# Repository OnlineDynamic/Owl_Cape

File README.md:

# Owl_Cape
Raspberry Pi (SMI Driven) FPP WS2811 based ch16 Pixel Controller Cape

Building on the great work of the Falcon FPP project, numerous open hardware pixel controllers and the clever brain behind this blog: https://iosoft.blog/2020/09/29/raspberry-pi-multi-channel-ws2812/

This project is looking to create a simple low cost 16ch Raspberry PI Cape to run on FPP using SMI interface of a 'Raspberry Pi Zero 2 W' (and potentially then expand out to supporting other Pi's with the 40PIN Header).  The aspiration is for the final code for the cape to be included in the FPP project and the xLights project to make a low cost easy to use pixel controller for LED pixel light shows which will benefit as the FPP project evolves its functionality.

## Basic Spec of Cape

- 12V DC in only (fused at xx Amps)
- PI Mounts on PCB
- 40 Pin Header for attaching to RPI via a ribbon cable (allow easy removal of PI)
- Power the RPI via Header pins
- 16 Ch of LED (WS2811) outputs individually fused at 5A running at 12V DC with SMD LED power indicators
- EEPROM onboard to identify CAPE to PI

## Potential Future expansion
- On board RJ45 Jack to connect wired ethernet to PI using USB test pads on PI
- Jumper to make LED voltage either 12V or 5V DC
- Basic LED Screen showing status

## Out of scope
- Any differential outputs

## Special Thanks to:
https://github.com/Kosh42/PCB-Designs/tree/main/Mirage for the inspiration

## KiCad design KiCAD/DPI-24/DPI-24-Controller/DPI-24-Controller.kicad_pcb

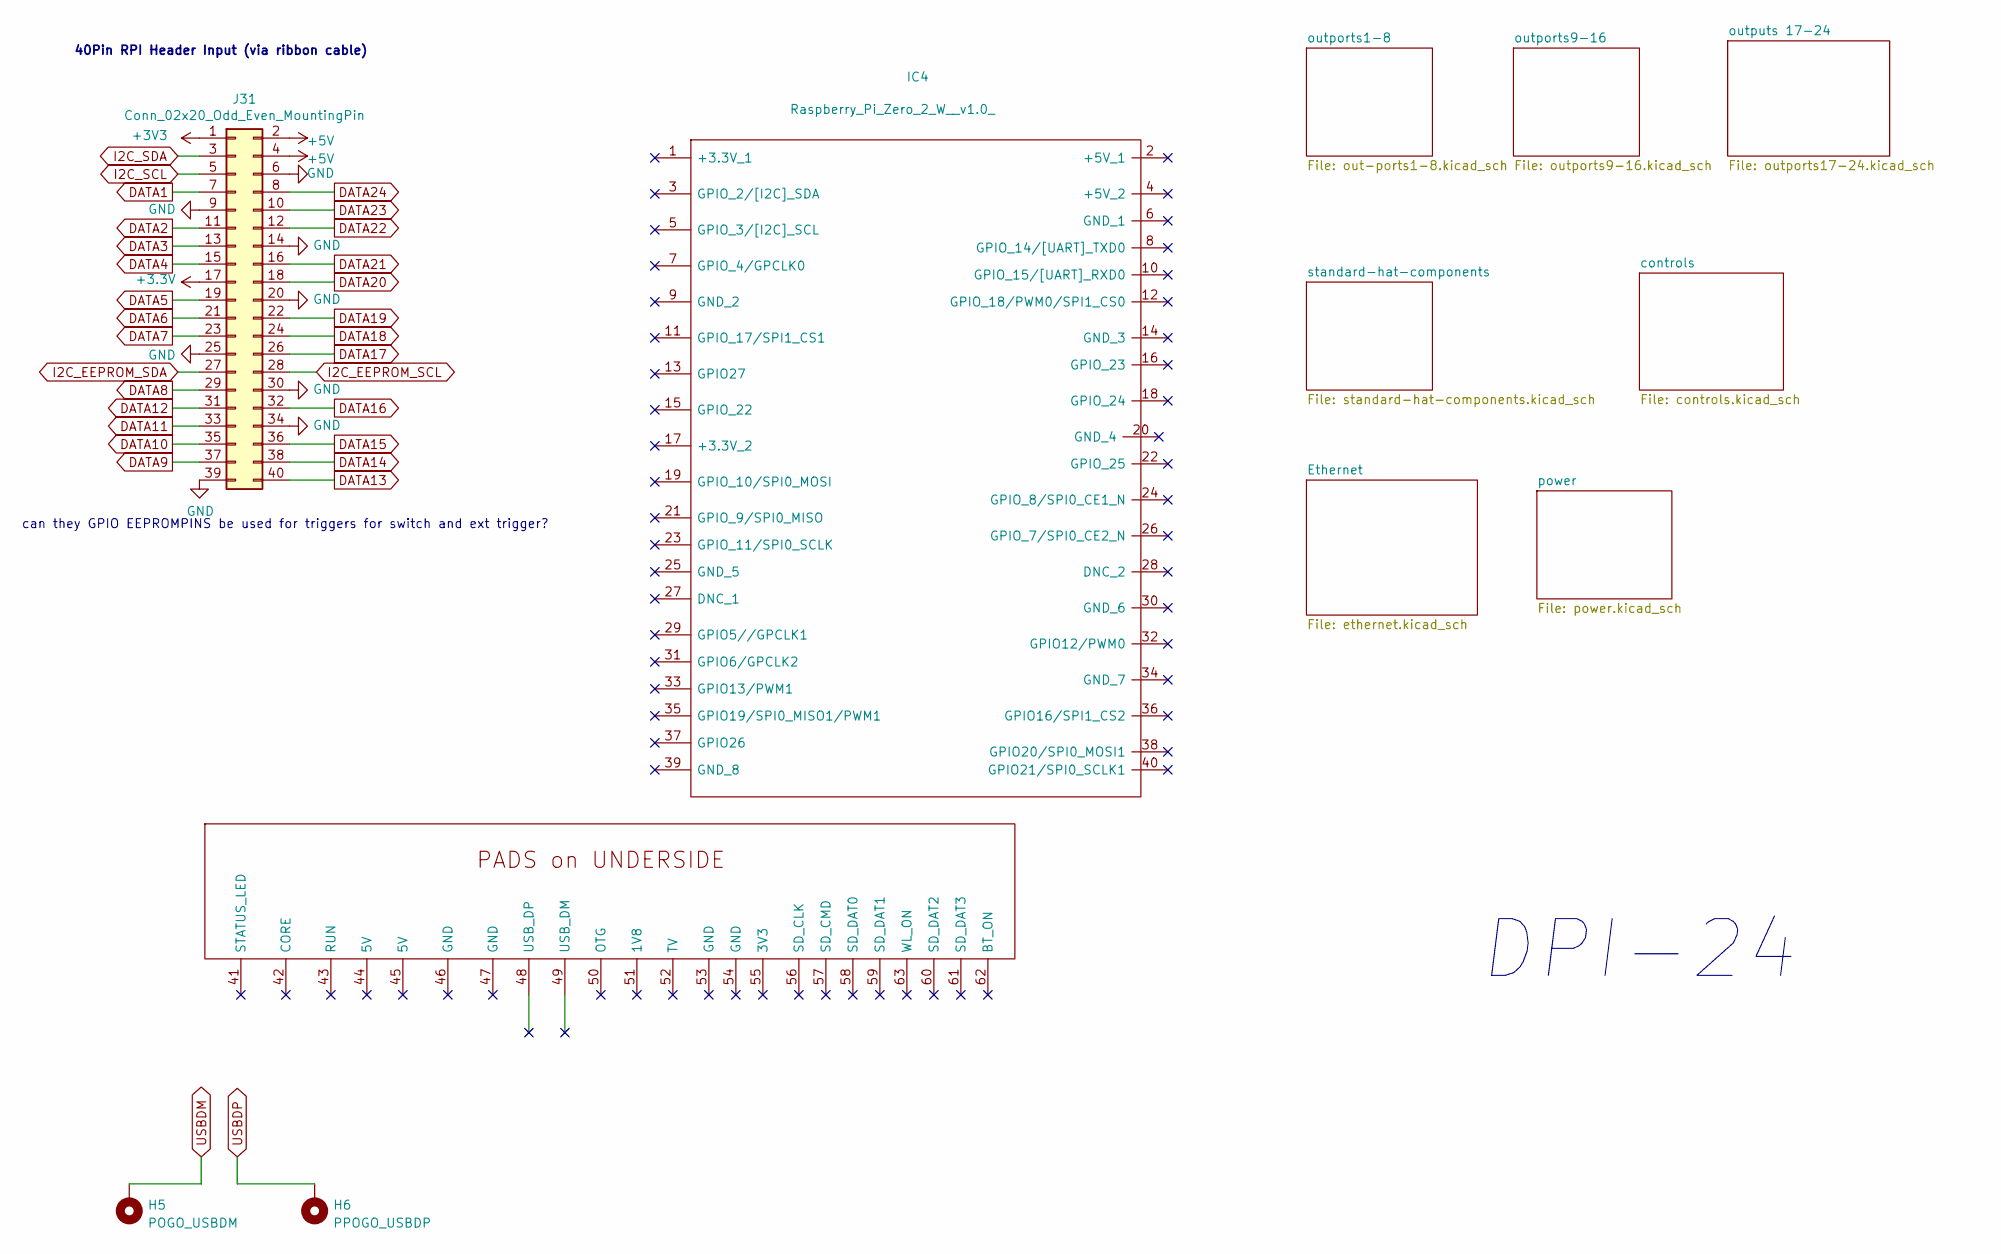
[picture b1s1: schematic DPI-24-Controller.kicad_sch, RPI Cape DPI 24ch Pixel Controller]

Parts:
H5: POGO_USBDM; POGO_D3.50mm_Drill0.9mm
H6: PPOGO_USBDP; POGO_D3.50mm_Drill0.9mm
IC4: Raspberry_Pi_Zero_2_W__v1.0_; RASPBERRYPIZERO2WV1; Manufacturer_Part_Number Raspberry Pi Zero 2 W (v1.0)
J31: Conn_02x20_Odd_Even_MountingPin; PinHeader_2x20_P2.54mm_Vertical

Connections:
DATA1: J31.7; also elsewhere on the board
DATA2: J31.11; also elsewhere on the board
DATA3: J31.13; also elsewhere on the board
DATA4: J31.15; also elsewhere on the board
DATA5: J31.19; also elsewhere on the board
DATA6: J31.21; also elsewhere on the board
DATA7: J31.23; also elsewhere on the board
DATA8: J31.29; also elsewhere on the board
DATA9: J31.37; also elsewhere on the board
DATA10: J31.35; also elsewhere on the board
DATA11: J31.33; also elsewhere on the board
DATA12: J31.31; also elsewhere on the board
DATA13: J31.40; also elsewhere on the board
DATA14: J31.38; also elsewhere on the board
DATA15: J31.36; also elsewhere on the board
DATA16: J31.32; also elsewhere on the board
DATA17: J31.26; also elsewhere on the board
DATA18: J31.24; also elsewhere on the board
DATA19: J31.22; also elsewhere on the board
DATA20: J31.18; also elsewhere on the board
DATA21: J31.16; also elsewhere on the board
DATA22: J31.12; also elsewhere on the board
DATA23: J31.10; also elsewhere on the board
DATA24: J31.8; also elsewhere on the board
I2C_EEPROM_SCL: J31.28; also elsewhere on the board
I2C_EEPROM_SDA: J31.27; also elsewhere on the board
I2C_SCL: J31.5; also elsewhere on the board
I2C_SDA: J31.3; also elsewhere on the board

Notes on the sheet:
can they GPIO EEPROMPINS be used for triggers for switch and ext trigger?
DPI-24
40Pin RPI Header Input (via ribbon cable)

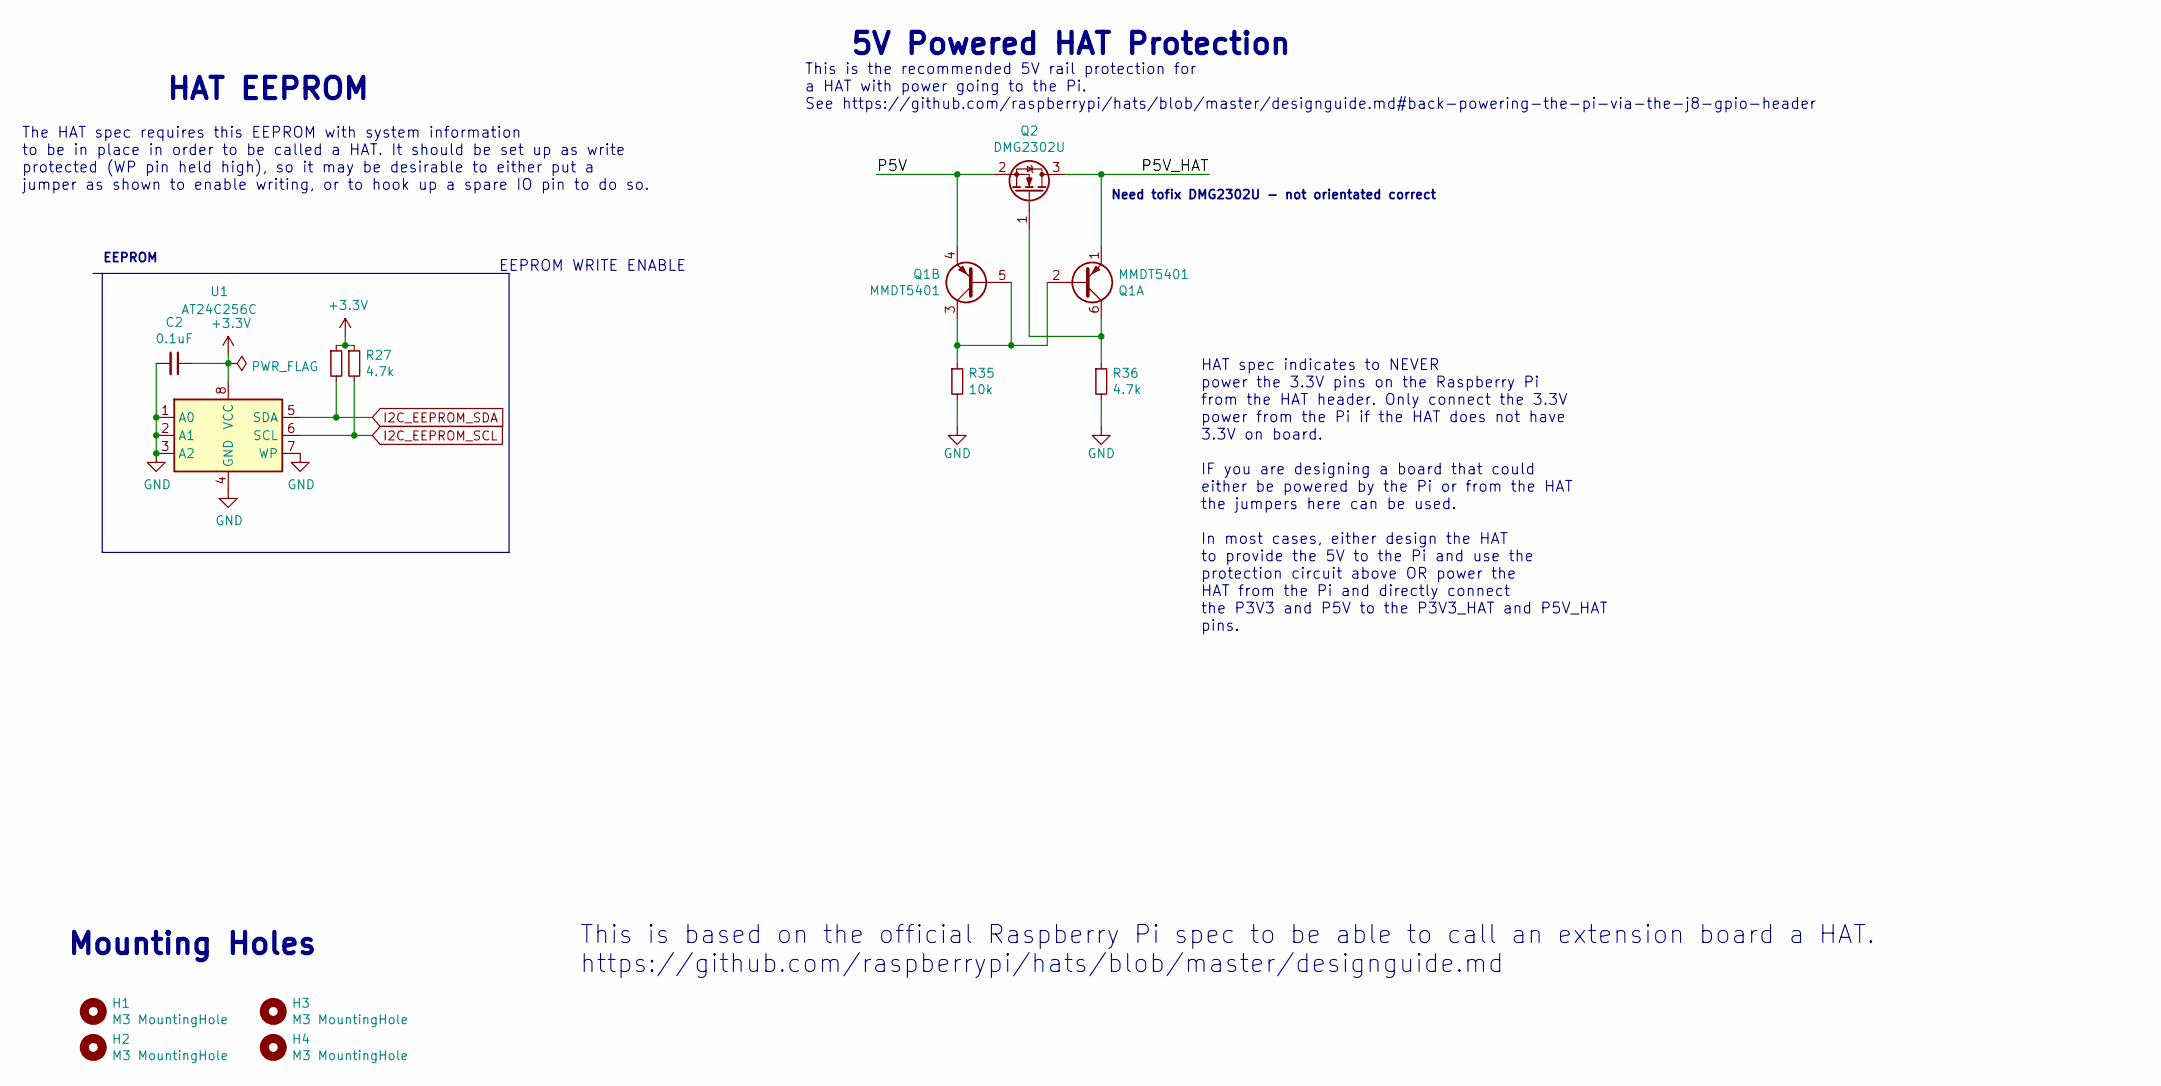
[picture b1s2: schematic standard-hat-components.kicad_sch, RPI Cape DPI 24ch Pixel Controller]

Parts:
C2: 0.1uF; C_Radial_D5.0mm_H11.0mm_P2.00mm
H1, H2, H3, H4: M3 MountingHole; MountingHole_3.2mm_M3_Pad_TopBottom
Q1: MMDT5401; SOT-363_SC-70-6
Q2: DMG2302U; SOT-23
R25, R27, R36: 4.7k; R_0805_2012Metric
R35: 10k; R_0805_2012Metric
U1: AT24C256C; DIP-8_W7.62mm_Socket

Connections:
/standard-hat-components/P5V: Q1.4 (E2), Q2.2 (S)
/standard-hat-components/P5V_HAT: Q1.1 (E1), Q2.3 (D)
I2C_EEPROM_SCL: R27.2, U1.6 (SCL); also elsewhere on the board
I2C_EEPROM_SDA: R25.2, U1.5 (SDA); also elsewhere on the board
unnamed: Q1.2 (B1), Q1.3 (C2), Q1.5 (B2), R35.1
unnamed: Q1.6 (C1), Q2.1 (G), R36.1

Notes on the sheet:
5V Powered HAT Protection
This is based on the official Raspberry Pi spec to be able to call an extension board a HAT. https://github.com/raspberrypi/hats/blob/master/designguide.md
Mounting Holes
EEPROM
HAT spec indicates to NEVER power the 3.3V pins on the Raspberry Pi from the HAT header. Only connect the 3.3V power from the Pi if the HAT does not have 3.3V on board. IF you are designing a board that could either be powered by the Pi or from the HAT the jumpers here can be used. In most cases, e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
HAT EEPROM
EEPROM WRITE ENABLE
Need tofix DMG2302U - not orientated correct
The HAT spec requires this EEPROM with system information to be in place in order to be called a HAT. It should be set up as write protected (WP pin held high), so it may be desirable to either put a jumper as shown to enable writing, or to hook up a spare IO pin to do so.
This is the recommended 5V rail protection for a HAT with power going to the Pi. See https://github.com/raspberrypi/hats/blob/master/designguide.md#back-powering-the-pi-via-the-j8-gpio-header

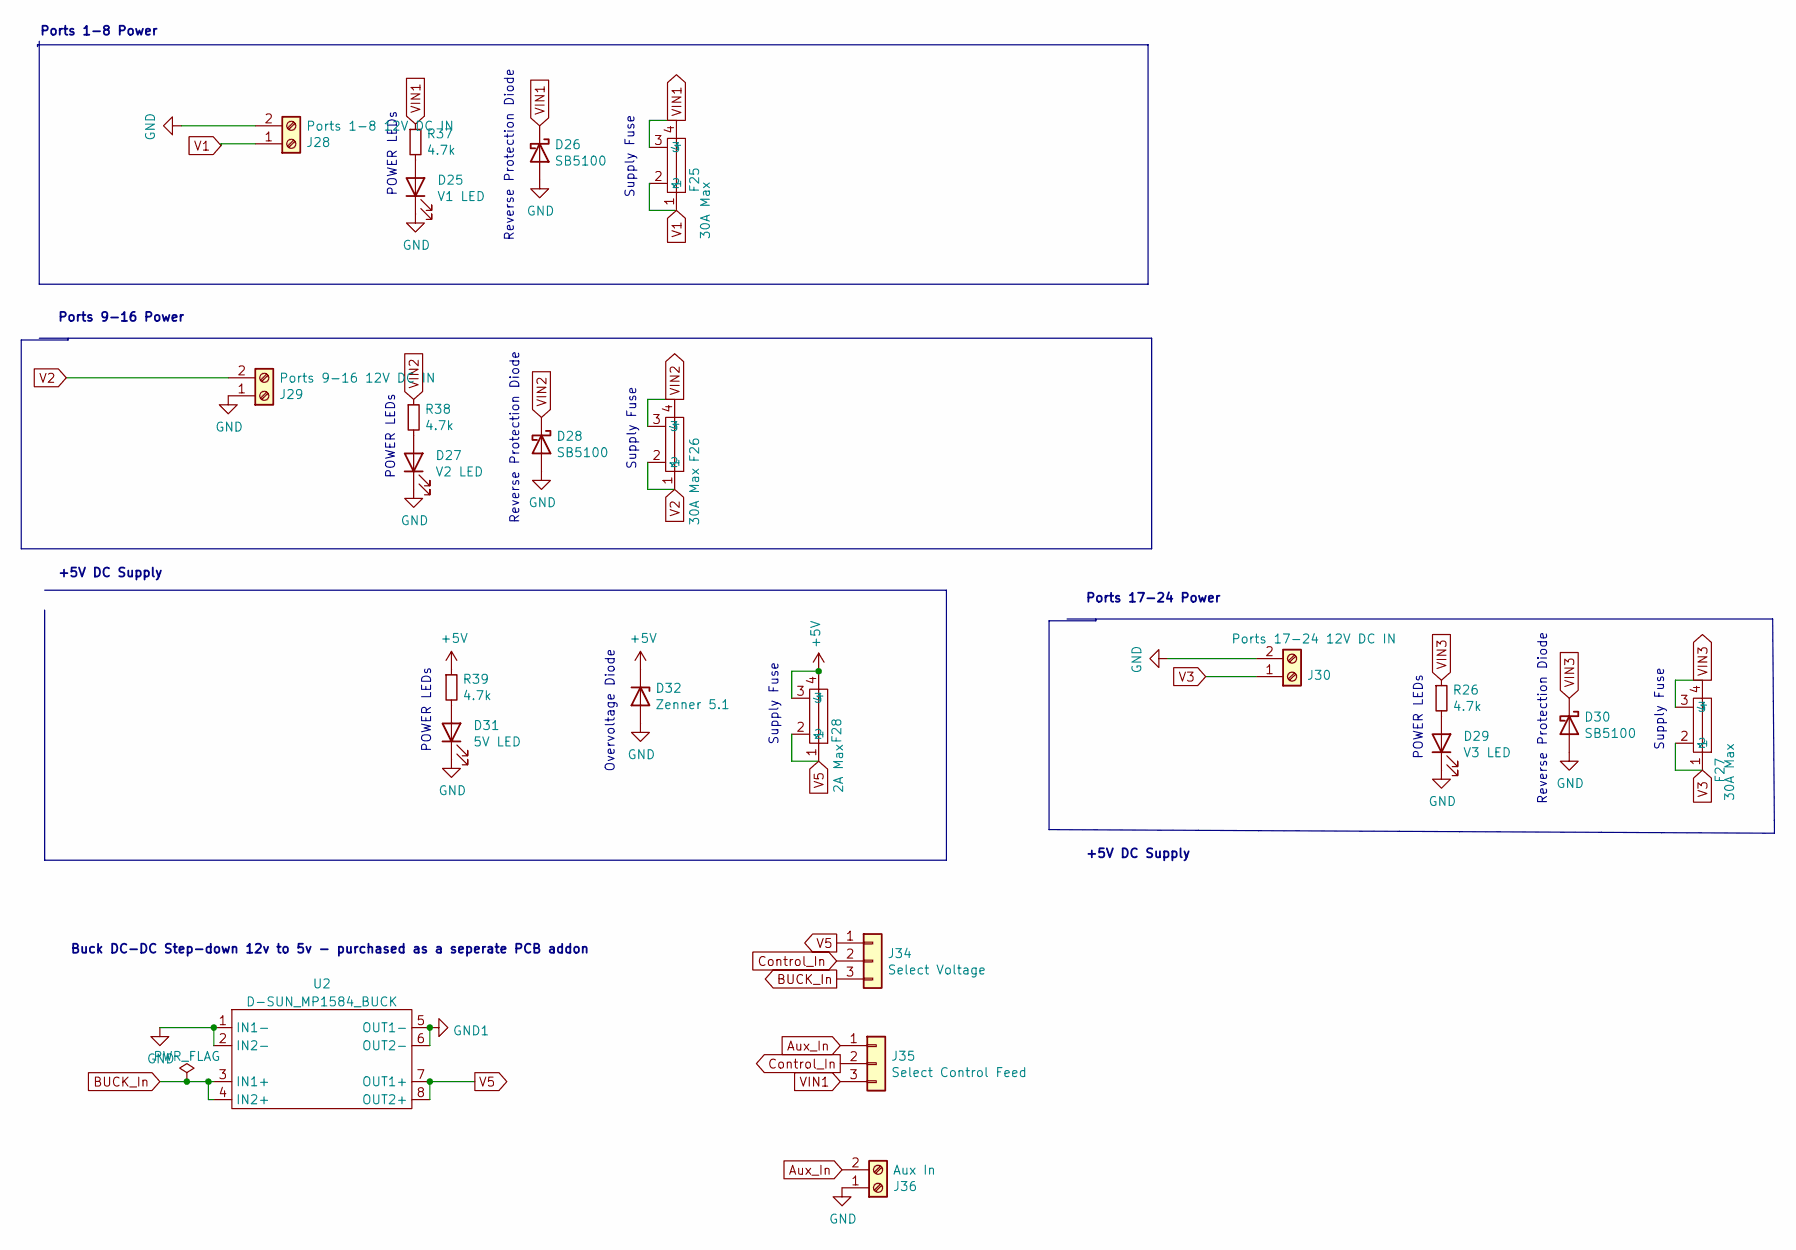
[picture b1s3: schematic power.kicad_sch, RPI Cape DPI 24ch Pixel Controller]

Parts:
D25: V1 LED; LED_0603_1608Metric
D26, D28, D30: SB5100; D_DO-201AD_P12.70mm_Horizontal
D27: V2 LED; LED_0603_1608Metric
D29: V3 LED; LED_0603_1608Metric
D31: 5V LED; LED_0603_1608Metric
D32: Zenner 5.1; D_5W_P10.16mm_Horizontal
F25, F26, F27: 30A Max; Medium Auto Fuse Holder
F28: 2A Max; Medium Auto Fuse Holder
J28: Ports 1-8 12V DC IN; TerminalBlock_KF950_1x02_P9.50mm_Horizontal
J29: Ports 9-16 12V DC IN; TerminalBlock_KF950_1x02_P9.50mm_Horizontal
J30: Ports 17-24 12V DC IN; TerminalBlock_KF950_1x02_P9.50mm_Horizontal
J34: Select Voltage; PinHeader_1x03_P2.54mm_Vertical
J35: Select Control Feed; PinHeader_1x03_P2.54mm_Vertical
J36: Aux In; TerminalBlock_RND_205-00012_1x02_P5.00mm_Horizontal
R26, R37, R38, R39: 4.7k; R_0805_2012Metric
U2: D-SUN_MP1584_BUCK

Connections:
Aux_In: J35.1, J36.2
BUCK_In: J34.3, U2.3 (IN1+), U2.4 (IN2+)
Control_In: J34.2, J35.2
GND1: U2.5 (OUT1-), U2.6 (OUT2-)
unnamed: D25.2 (A), R37.2
unnamed: D27.2 (A), R38.2
unnamed: D29.2 (A), R26.2
unnamed: D31.2 (A), R39.2
V1: F25.1, F25.2, J28.1
V2: F26.1, F26.2, J29.2
V3: F27.1, F27.2, J30.1
V5: F28.1, F28.2, J34.1, U2.7 (OUT1+), U2.8 (OUT2+)
VIN1: D26.1 (K), F25.3, F25.4, J35.3, R37.1; also elsewhere on the board
VIN2: D28.1 (K), F26.3, F26.4, R38.1; also elsewhere on the board
VIN3: D30.1 (K), F27.3, F27.4, R26.1; also elsewhere on the board

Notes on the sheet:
POWER LEDs
+5V DC Supply
Reverse Protection Diode
Supply Fuse
Ports 9-16 Power
Buck DC-DC Step-down 12v to 5v - purchased as a seperate PCB addon
Ports 17-24 Power
Ports 1-8 Power
Overvoltage Diode

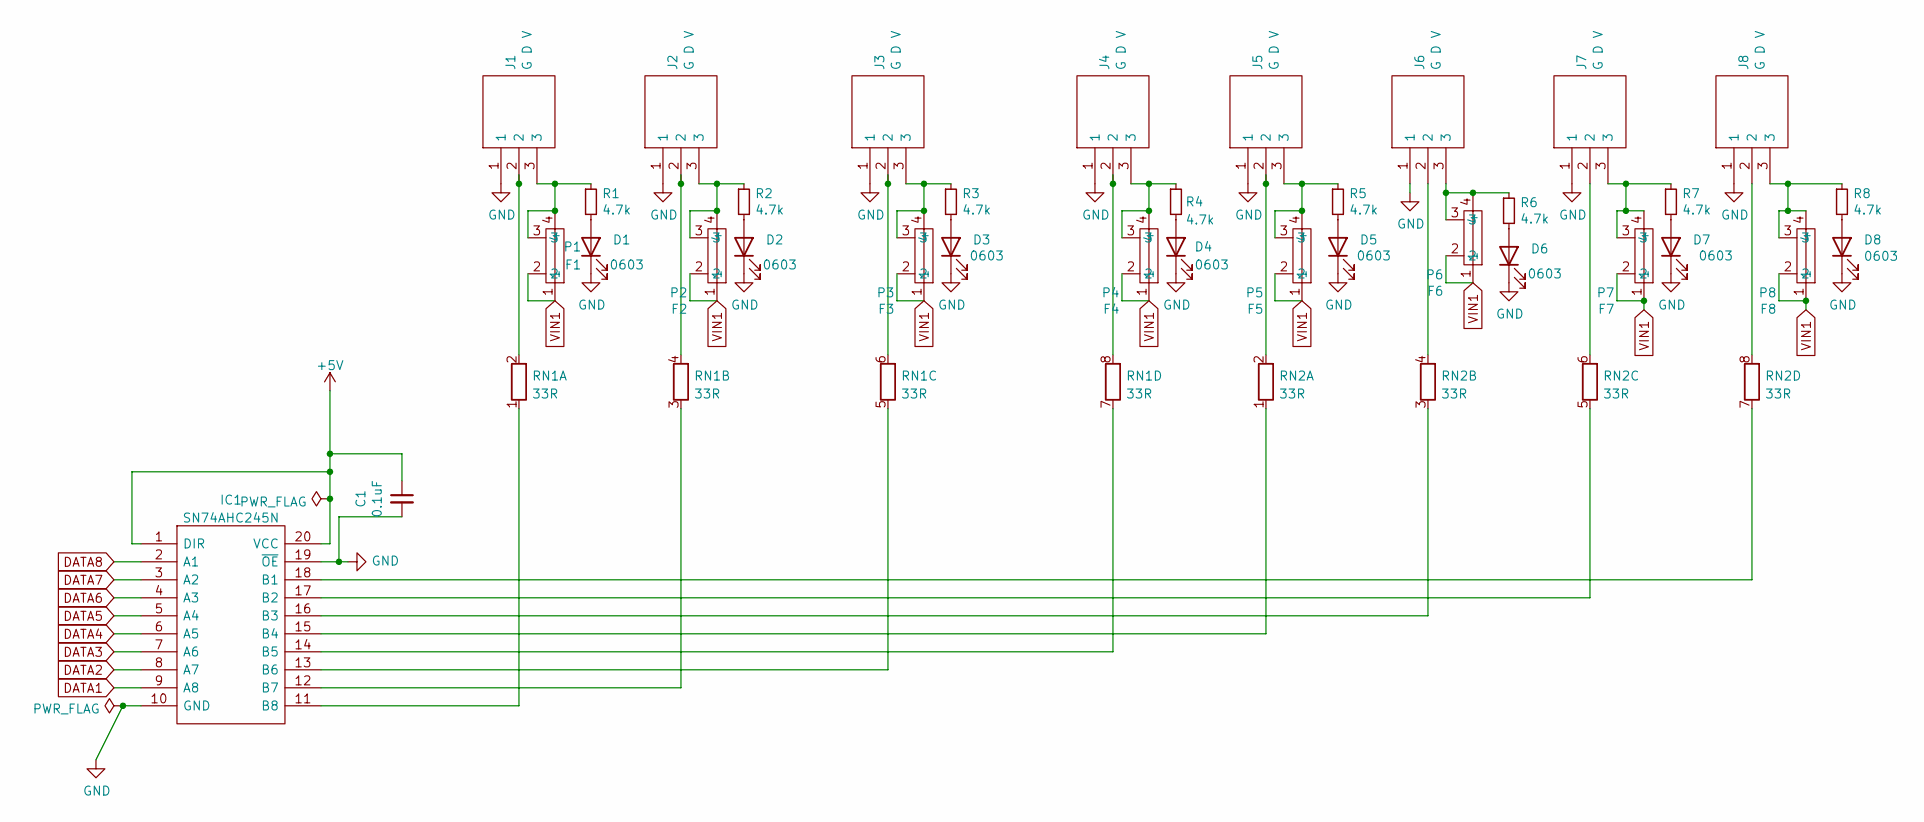
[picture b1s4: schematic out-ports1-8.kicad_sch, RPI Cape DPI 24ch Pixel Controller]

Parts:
C1: 0.1uF; C_Radial_D5.0mm_H11.0mm_P2.00mm
D1, D2, D3, D4, D5, D6, D7, D8: 0603; LED_0603_1608Metric
F1: P1; Medium Auto Fuse Holder
F2: P2; Medium Auto Fuse Holder
F3: P3; Medium Auto Fuse Holder
F4: P4; Medium Auto Fuse Holder
F5: P5; Medium Auto Fuse Holder
F6: P6; Medium Auto Fuse Holder
F7: P7; Medium Auto Fuse Holder
F8: P8; Medium Auto Fuse Holder
IC1: SN74AHC245N; DIP794W53P254L2540H508Q20N; Mouser Part Number 595-SN74AHC245N
J1, J2, J3, J4, J5, J6, J7, J8: G D V; PhoenixContact_MCV_1,5_3-G-3.5_1x03_P3.50mm_Vertical; Mouser Part Number 571-284514-3
R1, R2, R3, R4, R5, R6, R7, R8: 4.7k; R_0805_2012Metric
RN1, RN2: 33R; R_Array_SIP8

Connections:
DATA1: IC1.9 (A8); also elsewhere on the board
DATA2: IC1.8 (A7); also elsewhere on the board
DATA3: IC1.7 (A6); also elsewhere on the board
DATA4: IC1.6 (A5); also elsewhere on the board
DATA5: IC1.5 (A4); also elsewhere on the board
DATA6: IC1.4 (A3); also elsewhere on the board
DATA7: IC1.3 (A2); also elsewhere on the board
DATA8: IC1.2 (A1); also elsewhere on the board
unnamed: D1.2 (A), R1.2
unnamed: D2.2 (A), R2.2
unnamed: D3.2 (A), R3.2
unnamed: D4.2 (A), R4.2
unnamed: D5.2 (A), R5.2
unnamed: D6.2 (A), R6.2
unnamed: D7.2 (A), R7.2
unnamed: D8.2 (A), R8.2
unnamed: F1.3, F1.4, J1.3, R1.1
unnamed: F2.3, F2.4, J2.3, R2.1
unnamed: F3.3, F3.4, J3.3, R3.1
unnamed: F4.3, F4.4, J4.3, R4.1
unnamed: F5.3, F5.4, J5.3, R5.1
unnamed: F6.3, F6.4, J6.3, R6.1
unnamed: F7.3, F7.4, J7.3, R7.1
unnamed: F8.3, F8.4, J8.3, R8.1
unnamed: IC1.11 (B8), RN1.1 (R1.1)
unnamed: IC1.12 (B7), RN1.3 (R2.1)
unnamed: IC1.13 (B6), RN1.5 (R3.1)
unnamed: IC1.14 (B5), RN1.7 (R4.1)
unnamed: IC1.15 (B4), RN2.1 (R1.1)
unnamed: IC1.16 (B3), RN2.3 (R2.1)
unnamed: IC1.17 (B2), RN2.5 (R3.1)
unnamed: IC1.18 (B1), RN2.7 (R4.1)
unnamed: J1.2, RN1.2 (R1.2)
unnamed: J2.2, RN1.4 (R2.2)
unnamed: J3.2, RN1.6 (R3.2)
unnamed: J4.2, RN1.8 (R4.2)
unnamed: J5.2, RN2.2 (R1.2)
unnamed: J6.2, RN2.4 (R2.2)
unnamed: J7.2, RN2.6 (R3.2)
unnamed: J8.2, RN2.8 (R4.2)
VIN1: F1.1, F1.2, F2.1, F2.2, F3.1, F3.2, F4.1, F4.2, F5.1, F5.2, F6.1, F6.2, F7.1, F7.2, F8.1, F8.2; also elsewhere on the board

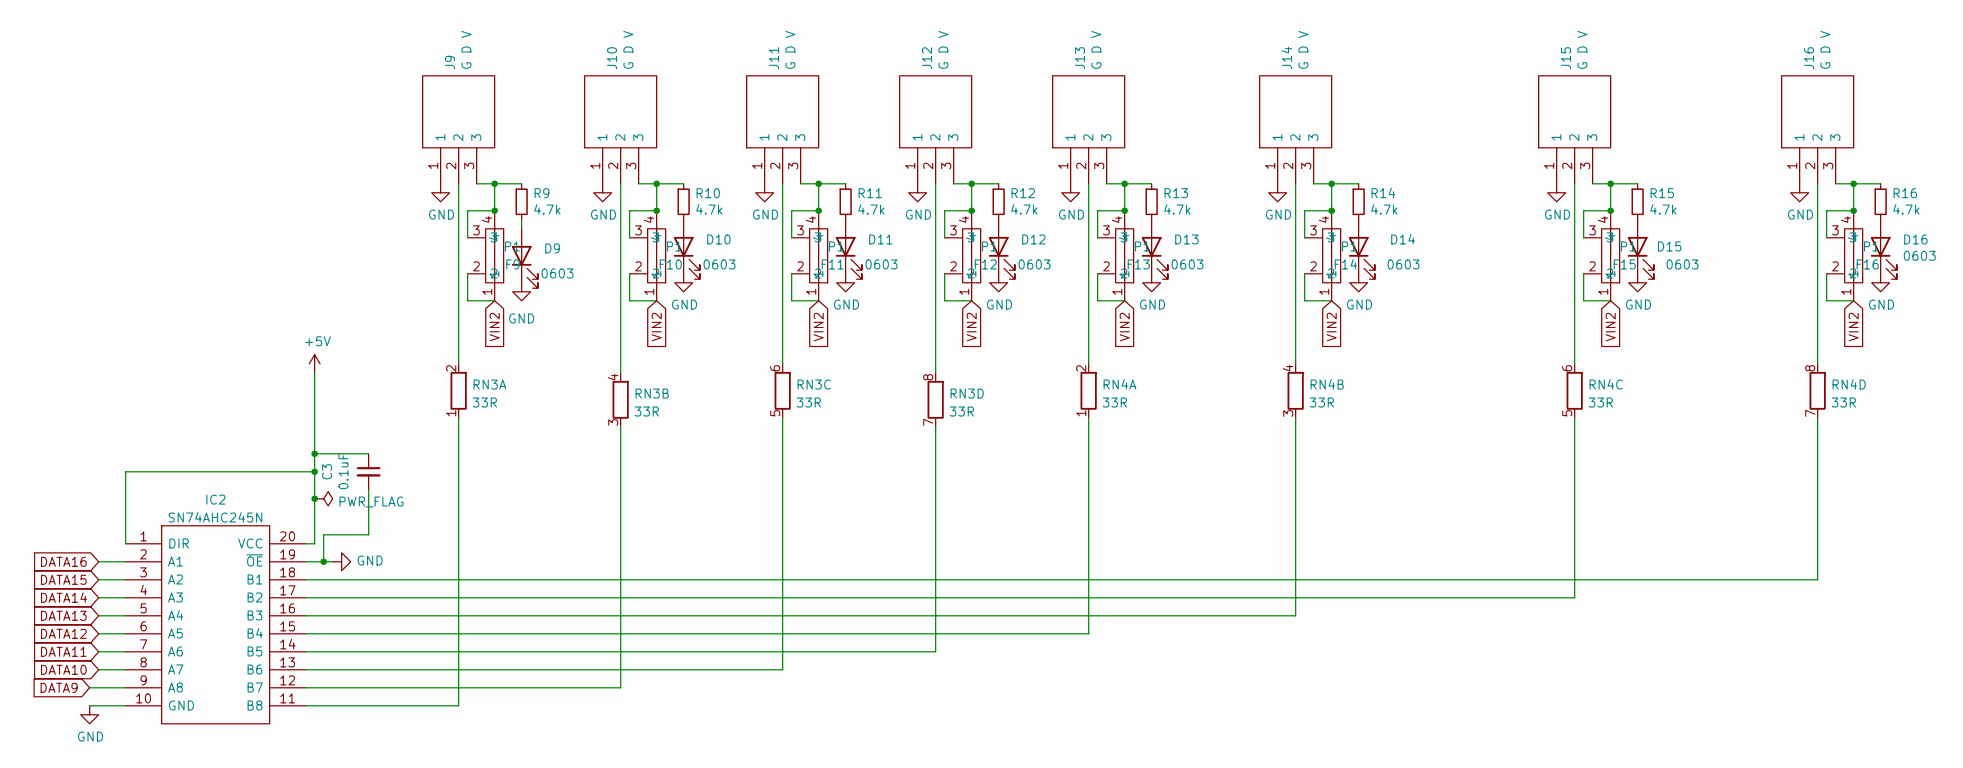
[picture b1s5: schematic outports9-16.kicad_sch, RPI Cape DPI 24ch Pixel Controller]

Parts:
C3: 0.1uF; C_Radial_D5.0mm_H11.0mm_P2.00mm
D9, D10, D11, D12, D13, D14, D15, D16: 0603; LED_0603_1608Metric
F9, F10, F11, F12, F13, F14, F15, F16: P1; Medium Auto Fuse Holder
IC2: SN74AHC245N; DIP794W53P254L2540H508Q20N; Mouser Part Number 595-SN74AHC245N
J9, J10, J11, J12, J13, J14, J15, J16: G D V; PhoenixContact_MCV_1,5_3-G-3.5_1x03_P3.50mm_Vertical; Mouser Part Number 571-284514-3
R9, R10, R11, R12, R13, R14, R15, R16: 4.7k; R_0805_2012Metric
RN3, RN4: 33R; R_Array_SIP8

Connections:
DATA9: IC2.9 (A8); also elsewhere on the board
DATA10: IC2.8 (A7); also elsewhere on the board
DATA11: IC2.7 (A6); also elsewhere on the board
DATA12: IC2.6 (A5); also elsewhere on the board
DATA13: IC2.5 (A4); also elsewhere on the board
DATA14: IC2.4 (A3); also elsewhere on the board
DATA15: IC2.3 (A2); also elsewhere on the board
DATA16: IC2.2 (A1); also elsewhere on the board
unnamed: D9.2 (A), R9.2
unnamed: D10.2 (A), R10.2
unnamed: D11.2 (A), R11.2
unnamed: D12.2 (A), R12.2
unnamed: D13.2 (A), R13.2
unnamed: D14.2 (A), R14.2
unnamed: D15.2 (A), R15.2
unnamed: D16.2 (A), R16.2
unnamed: F9.3, F9.4, J9.3, R9.1
unnamed: F10.3, F10.4, J10.3, R10.1
unnamed: F11.3, F11.4, J11.3, R11.1
unnamed: F12.3, F12.4, J12.3, R12.1
unnamed: F13.3, F13.4, J13.3, R13.1
unnamed: F14.3, F14.4, J14.3, R14.1
unnamed: F15.3, F15.4, J15.3, R15.1
unnamed: F16.3, F16.4, J16.3, R16.1
unnamed: IC2.11 (B8), RN3.1 (R1.1)
unnamed: IC2.12 (B7), RN3.3 (R2.1)
unnamed: IC2.13 (B6), RN3.5 (R3.1)
unnamed: IC2.14 (B5), RN3.7 (R4.1)
unnamed: IC2.15 (B4), RN4.1 (R1.1)
unnamed: IC2.16 (B3), RN4.3 (R2.1)
unnamed: IC2.17 (B2), RN4.5 (R3.1)
unnamed: IC2.18 (B1), RN4.7 (R4.1)
unnamed: J9.2, RN3.2 (R1.2)
unnamed: J10.2, RN3.4 (R2.2)
unnamed: J11.2, RN3.6 (R3.2)
unnamed: J12.2, RN3.8 (R4.2)
unnamed: J13.2, RN4.2 (R1.2)
unnamed: J14.2, RN4.4 (R2.2)
unnamed: J15.2, RN4.6 (R3.2)
unnamed: J16.2, RN4.8 (R4.2)
VIN2: F9.1, F9.2, F10.1, F10.2, F11.1, F11.2, F12.1, F12.2, F13.1, F13.2, F14.1, F14.2, F15.1, F15.2, F16.1, F16.2; also elsewhere on the board

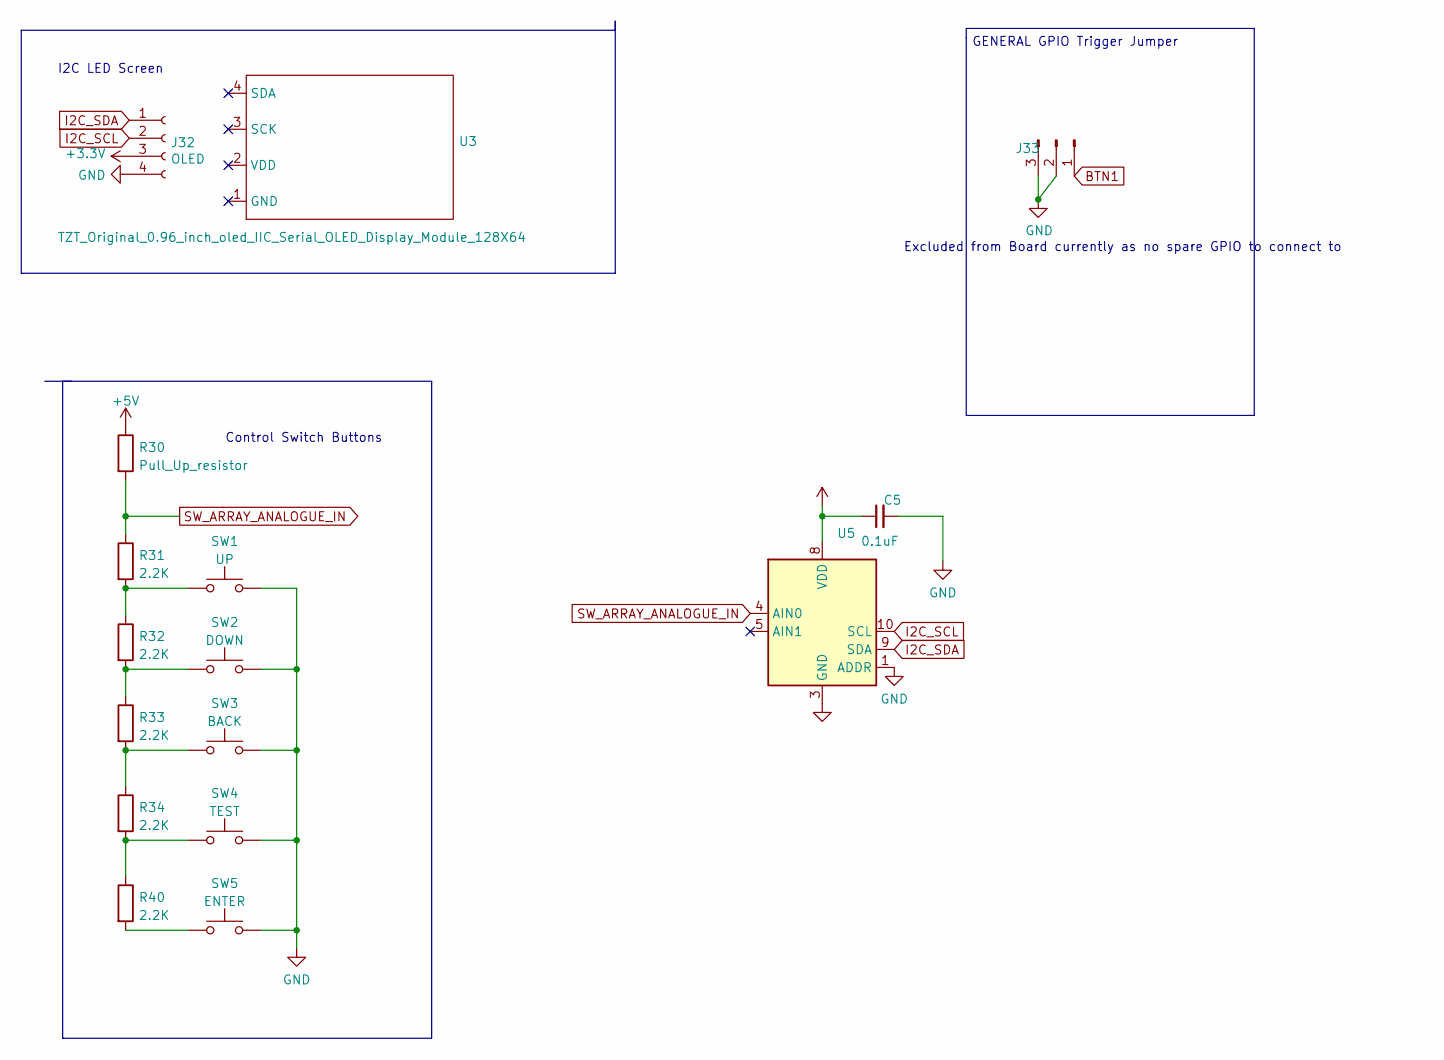
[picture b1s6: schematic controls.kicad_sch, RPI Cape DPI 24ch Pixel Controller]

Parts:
C5: 0.1uF; C_Radial_D5.0mm_H11.0mm_P2.00mm
J32: OLED; PinSocket_1x04_P2.54mm_Vertical
J33: (no value)
R30: Pull_Up_resistor; R_0805_2012Metric
R31, R32, R33, R34, R40: 2.2K; R_0805_2012Metric
SW1: UP; SW_PUSH_6mm
SW2: DOWN; SW_PUSH_6mm
SW3: BACK; SW_PUSH_6mm
SW4: TEST; SW_PUSH_6mm
SW5: ENTER; SW_PUSH_6mm
U3: TZT_Original_0.96_inch_oled_IIC_Serial_OLED_Displ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; TZT_0.96inch_OLED
U5: (no value)

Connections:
I2C_SCL: J32.2, U5.10 (SCL); also elsewhere on the board
I2C_SDA: J32.1, U5.9 (SDA); also elsewhere on the board
unnamed: R31.2, R32.1, SW1.1
unnamed: R32.2, R33.1, SW2.1
unnamed: R33.2, R34.1, SW3.1
unnamed: R34.2, R40.1, SW4.1
unnamed: R40.2, SW5.1
SW_ARRAY_ANALOGUE_IN: R30.2, R31.1, U5.4 (AIN0)

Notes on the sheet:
Excluded from Board currently as no spare GPIO to connect to
GENERAL GPIO Trigger Jumper
I2C LED Screen
Control Switch Buttons

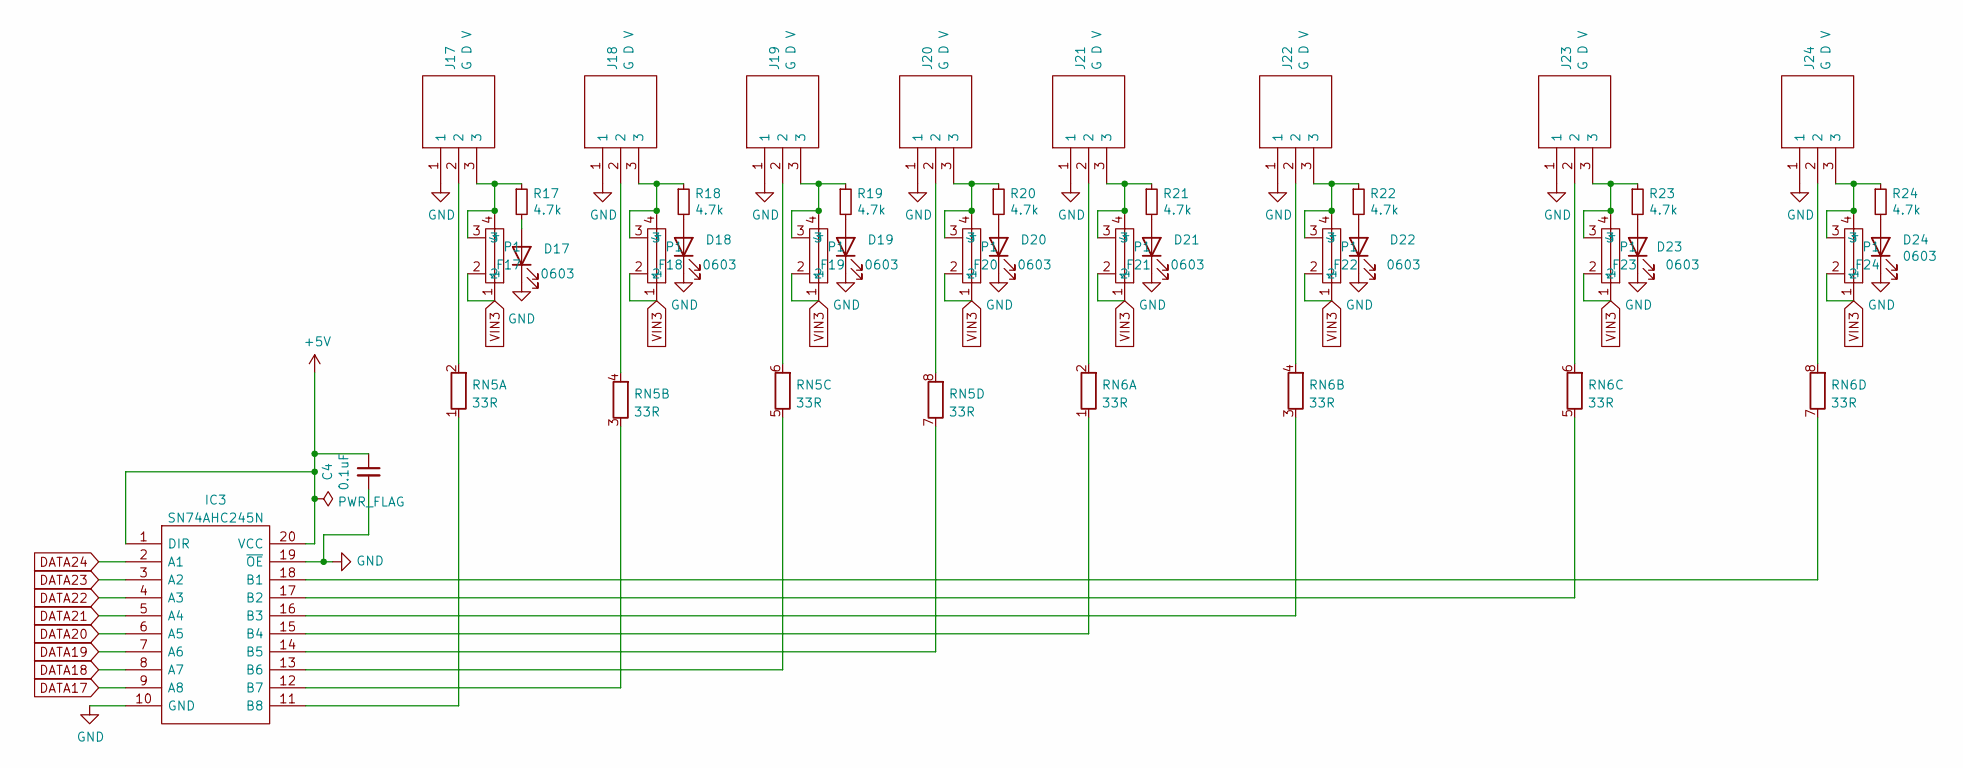
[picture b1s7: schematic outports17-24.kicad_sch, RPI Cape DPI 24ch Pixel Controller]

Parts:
C4: 0.1uF; C_Radial_D5.0mm_H11.0mm_P2.00mm
D17, D18, D19, D20, D21, D22, D23, D24: 0603; LED_0603_1608Metric
F17, F18, F19, F20, F21, F22, F23, F24: P1; Medium Auto Fuse Holder
IC3: SN74AHC245N; DIP794W53P254L2540H508Q20N; Mouser Part Number 595-SN74AHC245N
J17, J18, J19, J20, J21, J22, J23, J24: G D V; PhoenixContact_MCV_1,5_3-G-3.5_1x03_P3.50mm_Vertical; Mouser Part Number 571-284514-3
R17, R18, R19, R20, R21, R22, R23, R24: 4.7k; R_0805_2012Metric
RN5, RN6: 33R; R_Array_SIP8

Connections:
DATA17: IC3.9 (A8); also elsewhere on the board
DATA18: IC3.8 (A7); also elsewhere on the board
DATA19: IC3.7 (A6); also elsewhere on the board
DATA20: IC3.6 (A5); also elsewhere on the board
DATA21: IC3.5 (A4); also elsewhere on the board
DATA22: IC3.4 (A3); also elsewhere on the board
DATA23: IC3.3 (A2); also elsewhere on the board
DATA24: IC3.2 (A1); also elsewhere on the board
unnamed: D17.2 (A), R17.2
unnamed: D18.2 (A), R18.2
unnamed: D19.2 (A), R19.2
unnamed: D20.2 (A), R20.2
unnamed: D21.2 (A), R21.2
unnamed: D22.2 (A), R22.2
unnamed: D23.2 (A), R23.2
unnamed: D24.2 (A), R24.2
unnamed: F17.3, F17.4, J17.3, R17.1
unnamed: F18.3, F18.4, J18.3, R18.1
unnamed: F19.3, F19.4, J19.3, R19.1
unnamed: F20.3, F20.4, J20.3, R20.1
unnamed: F21.3, F21.4, J21.3, R21.1
unnamed: F22.3, F22.4, J22.3, R22.1
unnamed: F23.3, F23.4, J23.3, R23.1
unnamed: F24.3, F24.4, J24.3, R24.1
unnamed: IC3.11 (B8), RN5.1 (R1.1)
unnamed: IC3.12 (B7), RN5.3 (R2.1)
unnamed: IC3.13 (B6), RN5.5 (R3.1)
unnamed: IC3.14 (B5), RN5.7 (R4.1)
unnamed: IC3.15 (B4), RN6.1 (R1.1)
unnamed: IC3.16 (B3), RN6.3 (R2.1)
unnamed: IC3.17 (B2), RN6.5 (R3.1)
unnamed: IC3.18 (B1), RN6.7 (R4.1)
unnamed: J17.2, RN5.2 (R1.2)
unnamed: J18.2, RN5.4 (R2.2)
unnamed: J19.2, RN5.6 (R3.2)
unnamed: J20.2, RN5.8 (R4.2)
unnamed: J21.2, RN6.2 (R1.2)
unnamed: J22.2, RN6.4 (R2.2)
unnamed: J23.2, RN6.6 (R3.2)
unnamed: J24.2, RN6.8 (R4.2)
VIN3: F17.1, F17.2, F18.1, F18.2, F19.1, F19.2, F20.1, F20.2, F21.1, F21.2, F22.1, F22.2, F23.1, F23.2, F24.1, F24.2; also elsewhere on the board
